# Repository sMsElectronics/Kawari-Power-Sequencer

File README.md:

# PC Boards available here: 
## [sMs Retro Electronics KoFi Shop](https://ko-fi.com/smsretroelectronics)

The Kawari Power Sequencer, known from here on as the “KPS”, is an electronically switched 5V regulator module that has been designed specifically for the EVO64 motherboard to work along side a Kawari VIC II and MSM. The KPS is a reliable, efficient, low noise, high frequency 5V switching regulator which remains very cool unlike linear regulators IC’s such as the common 7805. 

The KPS is installed onto the EVO64 motherboard’s 5V “CAN” regulator location that supplies power only to the VIC II 5V VCC socket pin.

The KPS allows the user to switch video standards on your EVO64 Commodore 64 between NTSC and PAL via the “Multi-Switch Module” MSM and a Kawari VIC II LARGE or SMALL board using a simple keyboard command. It will switch the video standard and recycle the Kawari’s power in one operation. No longer will the user have to manually switch the computers power OFF and ON after setting the video standard with an MSM. 

The KPS incorporates an over current sensing circuit that will sense when the output current goes above 780 mA and turns the 5V output off. A RED LED will indicate this condition. The KPS will remain latched in over current state until the input voltage is turned off and the over current condition is removed.  

sMs Retro Electronics A Division of sMs Electronics 2025
# LED Indicators: 

|LED|COLOR|DESCRIPTION
|:--:|:--|:--|
|D1|BLUE|REGULATOR 5V
|D2|RED|OVER CURRENT 
|D3|GREEN|KAWARI 5V   

 # KPS wiring details

# Detailed Wiring:

 # KPS Firmware operation

The purpose of the KPS firmware is to allow the Kawari VICII hardware emulator to switch between NTSC and PAL video modes when commanded by an Retrospective EVO64 MSM controller without the need to recycle the computer power. It also provides an OVER CURRENT feature that will switch the power OFF to the Kawari if the current is >= 780 milliamperes. 

The firmware is essentially a state machine that monitors for any change, either a rising or falling edge, from the NTSC (or the PAL) logic output of the MSM and electronically cycles the power OFF then ON to the Kawari Vcc pin. This cycle is as follows: Turn power OFF when a change is detected, keep the power off until the boards RESET is asserted, at this point the power is returned to ON. The NTSC (or the PAL) logic output from the MSM is also routed to the Kawari video select pin header via an open drain MOSFET for 5V to 3.3V translation. 

Over current is latching. If an over current condition is detected, the firmware will turn the power OFF to the Kawari Vcc pin and remain OFF until the next system power cycle. all status is indicated with different color LED's 

 # KPS Build Notes & Cautions 

 If you are building your own KPS, make sure you flash U2 MCU with the firmware provided. All the instructions are provided in the "Flashing and HEX File" folder. When building your KPS, *it is recommended that you populate all components except your programmed U2 ATtiny85V-10S MCU and U3 AP2152A electronic power switch.* This is to prevent damage to these chips in cases where the regulator is not working properly due to errors in construction. These errors can lead to over voltage conditions that will easily damage your chips. It is recommended on first power up to check if the BLUE LED is ON and to measure the core regulator output voltage and check if its 5V +/- 5%. If it is not, then investigate why.    

# PCB V1.0 Silkscreen Errata 

Silkscreen anode indication for D3 is incorrect. If D3 is installed as per the silkscreen, the diode will not illuminate. 

# Change FROM:
  
# Change TO:

Be sure to check out the full documentation ! PCB's will be available soon on my KoFi shop.

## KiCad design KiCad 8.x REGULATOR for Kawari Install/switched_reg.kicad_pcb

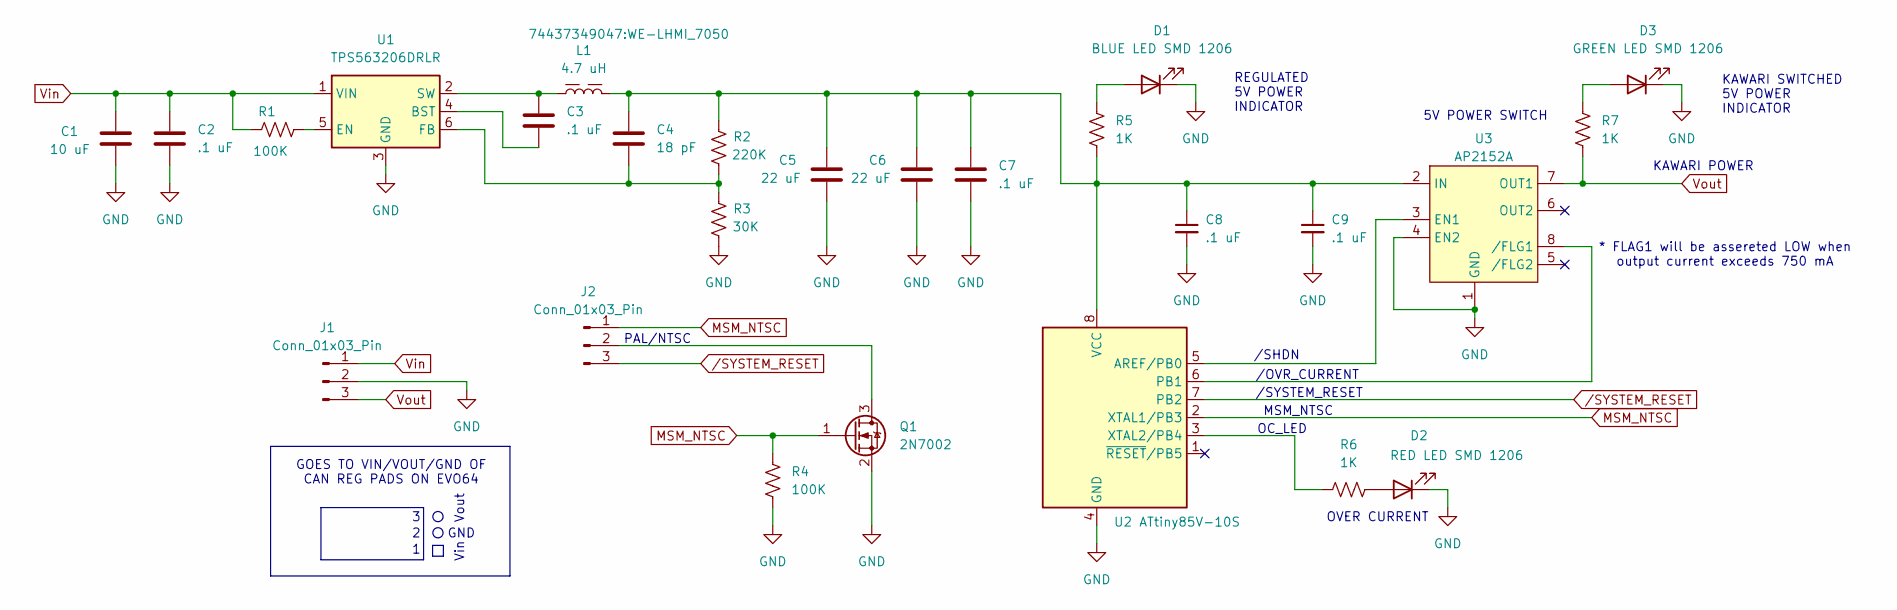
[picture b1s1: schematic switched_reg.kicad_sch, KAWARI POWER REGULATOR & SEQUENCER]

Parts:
C1: 10 uF; C_0805_2012Metric
C2, C3, C7, C8, C9: .1 uF; C_0805_2012Metric
C4: 18 pF; C_0805_2012Metric
C5, C6: 22 uF; C_0805_2012Metric
D1: BLUE LED SMD 1206; LED_1206_3216Metric
D2: RED LED SMD 1206; LED_1206_3216Metric
D3: GREEN LED SMD 1206; LED_1206_3216Metric
J1, J2: Conn_01x03_Pin; PinHeader_1x03_P2.54mm_Vertical
L1: 4.7 uH; WE-LHMI_7050
Q1: 2N7002; SOT-23
R1, R4: 100K; R_0805_2012Metric
R2: 220K; R_0805_2012Metric
R3: 30K; R_0805_2012Metric
R5, R6, R7: 1K; R_0805_2012Metric
U1: TPS563206DRLR; SOT-563
U2: ATtiny85V-10S; SOIC-8W_5.3x5.3mm_P1.27mm
U3: AP2152A; SO-8_3.9x4.9mm_P1.27mm

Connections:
GND: C1.2, C2.2, C5.2, C6.2, C7.2, C8.2, C9.2, D1.1 (K), D2.1 (K), D3.1 (K), J1.2, Q1.2 (S), R3.2, R4.2, U1.3 (GND), U2.4 (GND), U3.1 (GND), U3.4 (EN2)
MSM_NTSC: J2.1, Q1.1 (G), R4.1, U2.2 (XTAL1/PB3)
unnamed: D1.2 (A), R5.1
unnamed: D2.2 (A), R6.2
unnamed: D3.2 (A), R7.1
unnamed: J2.2, Q1.3 (D)
unnamed: C3.2, U1.4 (BST)
unnamed: R1.2, U1.5 (EN)
unnamed: C4.2, R2.2, R3.1, U1.6 (FB)
unnamed: C3.1, L1.1, U1.2 (SW)
unnamed: U2.5 (AREF/PB0), U3.3 (EN1)
unnamed: U2.6 (PB1), U3.8 (/FLG1)
unnamed: C4.1, C5.1, C6.1, C7.1, C8.1, C9.1, L1.2, R2.1, R5.2, U2.8 (VCC), U3.2 (IN)
unnamed: R6.1, U2.3 (XTAL2/PB4)
Vin: C1.1, C2.1, J1.1, R1.1, U1.1 (VIN)
Vout: J1.3, R7.2, U3.7 (OUT1)
/SYSTEM_RESET: J2.3, U2.7 (PB2)

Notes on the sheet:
* FLAG1 will be assereted LOW when output current exceeds 750 mA
MSM_NTSC
/OVR_CURRENT
GOES TO VIN/VOUT/GND OF CAN REG PADS ON EVO64
Vin
/SHDN
5V POWER SWITCH
Vout
KAWARI POWER
KAWARI SWITCHED 5V POWER INDICATOR
GND
OVER CURRENT
OC_LED
/SYSTEM_RESET
REGULATED 5V POWER INDICATOR
PAL/NTSC

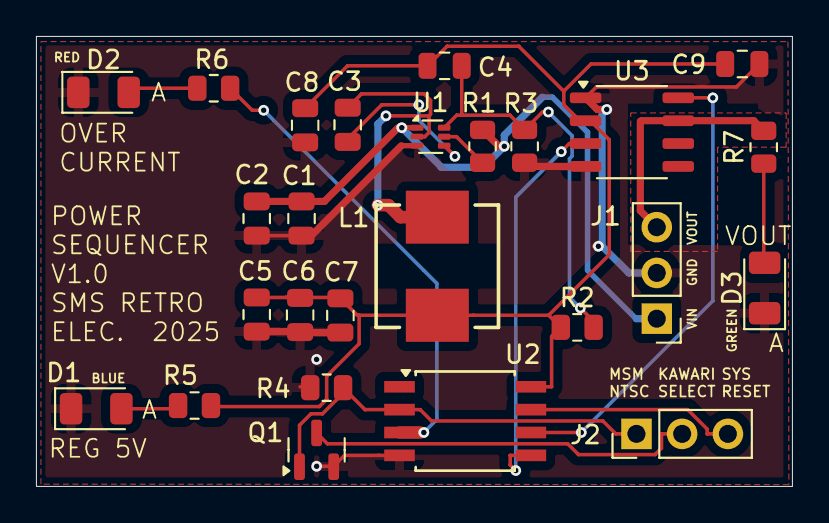
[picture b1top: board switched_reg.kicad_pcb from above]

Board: 2 copper layers, 42.0 x 25.0 mm, 26 parts (0 on the bottom side), 17 nets.

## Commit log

2025-04-09 Added more build Instructions & Files
    Added more build Instructions & Files
2025-04-09 Added Company Name
    Added to readme.md
2025-04-09 Added LICENSE File
    Added a LICENSE file and a link in my readme.md file to my shop.
2025-04-14 BOM Changes
    Added and corrected part numbers. Added part descriptions
